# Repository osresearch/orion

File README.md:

Orion PCB
===

The layout is based on [Orion constellation with star labels](https://commons.wikimedia.org/wiki/File:Orion_constellation_with_star_labels.jpg) by Anirban Nandi(CC-BY).

Firmware and schematic is based on [20 LED charlieplexed pendant](https://github.com/osresearch/pendant).

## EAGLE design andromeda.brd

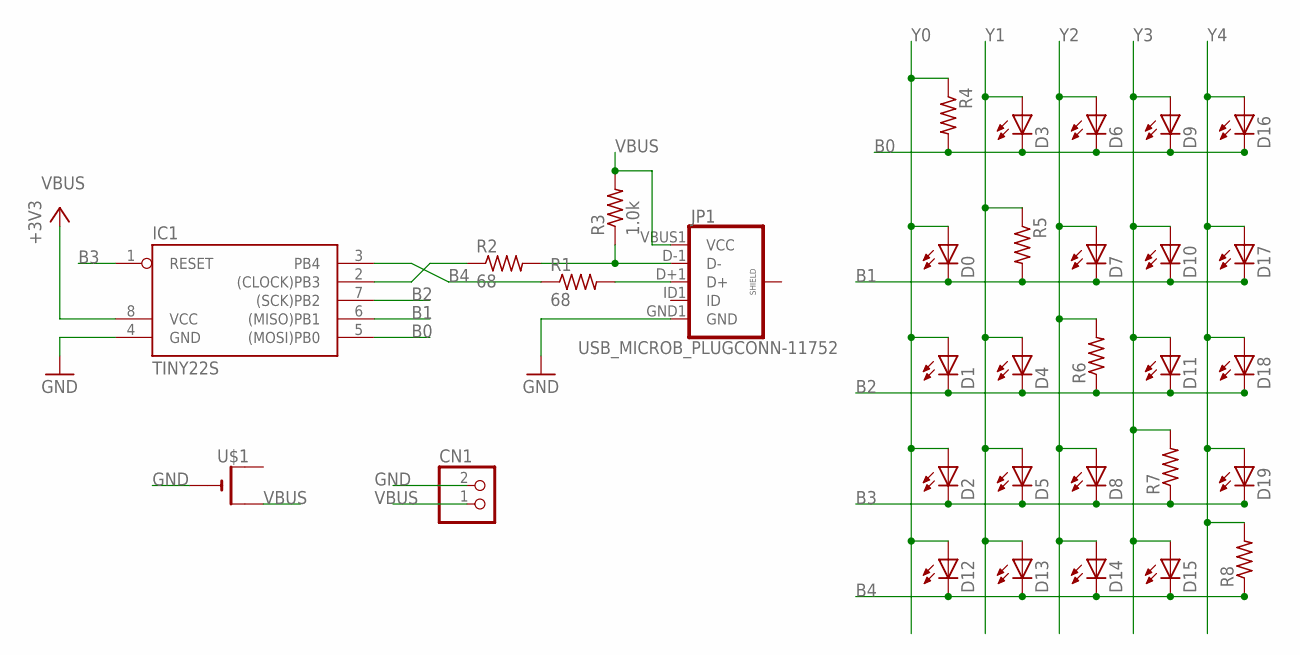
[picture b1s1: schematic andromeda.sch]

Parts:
CN1: JST_2PIN-THM-RA; JST-PH-2-THM-RA
D0, D1, D2, D3, D4, D5, D6, D7, D8, D9, D10, D11, D12, D13, D14, D15, D16, D17, D18, D19: LEDCHIPLED_0805; CHIPLED_0805
IC1: TINY22S; SOIC8
JP1: USB_MICROB_PLUGCONN-11752; USB-B-MICRO-SMD_V03
R1, R2: 68; R0603
R3: 1.0k; R0603
R4, R5, R6, R7, R8: R-US_R0603; R0603
U$1: CR2032SMT; CR2032-SMD

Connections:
B0: D3.C, D6.C, D9.C, D16.C, IC1.5 ((MOSI)PB0), R4.2
B1: D0.C, D7.C, D10.C, D17.C, IC1.6 ((MISO)PB1), R5.2
B2: D1.C, D4.C, D11.C, D18.C, IC1.7 ((SCK)PB2), R6.1
B3: D2.C, D5.C, D8.C, D19.C, IC1.1 (RESET), R7.1
B4: D12.C, D13.C, D14.C, D15.C, IC1.3 (PB4), R1.1, R8.1
GND: CN1.2 (1), IC1.4 (GND), JP1.GND1 (GND), U$1.-
unnamed: JP1.D+1 (D+), R1.2
unnamed: JP1.D-1 (D-), R2.2, R3.1
unnamed: IC1.2 ((CLOCK)PB3), R2.1
VBUS: CN1.1 (2), IC1.8 (VCC), JP1.VBUS1 (VCC), R3.2, U$1.+$2 (+1)
Y0: D0.A, D1.A, D2.A, D12.A, R4.1
Y1: D3.A, D4.A, D5.A, D13.A, R5.1
Y2: D6.A, D7.A, D8.A, D14.A, R6.2
Y3: D9.A, D10.A, D11.A, D15.A, R7.2
Y4: D16.A, D17.A, D18.A, D19.A, R8.2

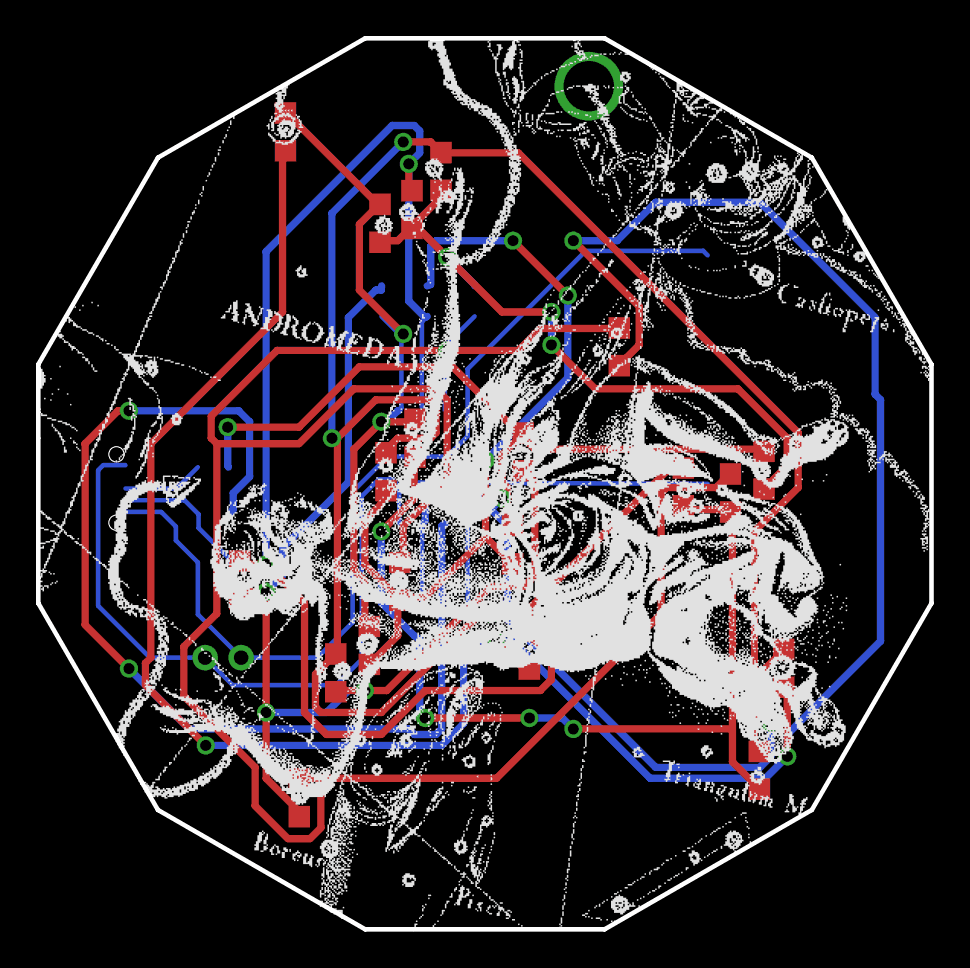
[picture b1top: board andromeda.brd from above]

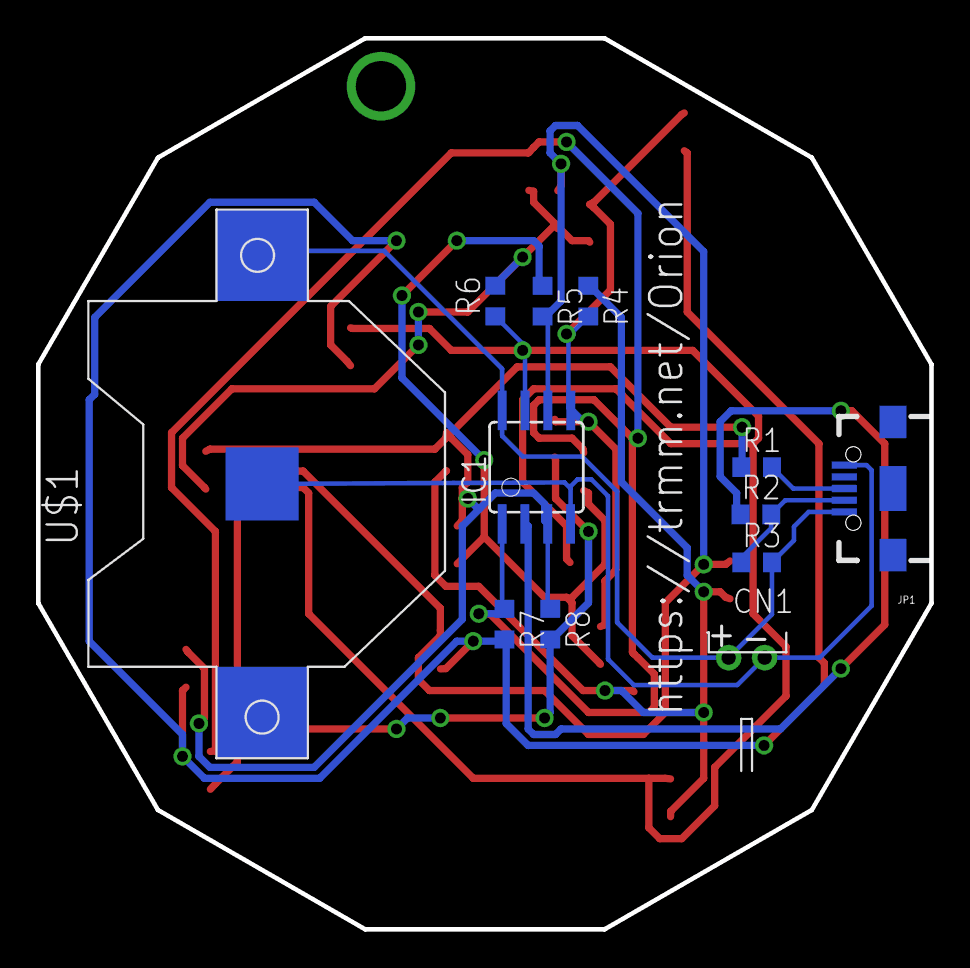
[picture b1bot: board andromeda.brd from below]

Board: 2 copper layers, 49.6 x 49.5 mm, 32 parts (12 on the bottom side), 15 nets.

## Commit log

2018-07-02 20 LED Orion board
2018-07-02 gradiant
2018-07-02 readme and links
2018-07-02 transparent background
2018-07-03 rename to orion
2018-07-03 andromeda board

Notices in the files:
parts and their libraries:
SparkFun-Connectors: Licensing: Creative Commons ShareAlike 4.0 International - https://creativecommons.org/licenses/by-sa/4.0
